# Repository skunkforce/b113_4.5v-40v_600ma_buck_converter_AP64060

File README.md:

# edgy_board number b113
This design is part of the [edgy board project](https://github.com/skunkforce/edgy_boards).  

# getting started
This repository uses submodules. After cloning use the command 

```$ git submodule update --init --recursive```

to pull the submodules before opening the project with kicad. 

# Tests
Tests can be found in [TESTS.md](TESTS.md)

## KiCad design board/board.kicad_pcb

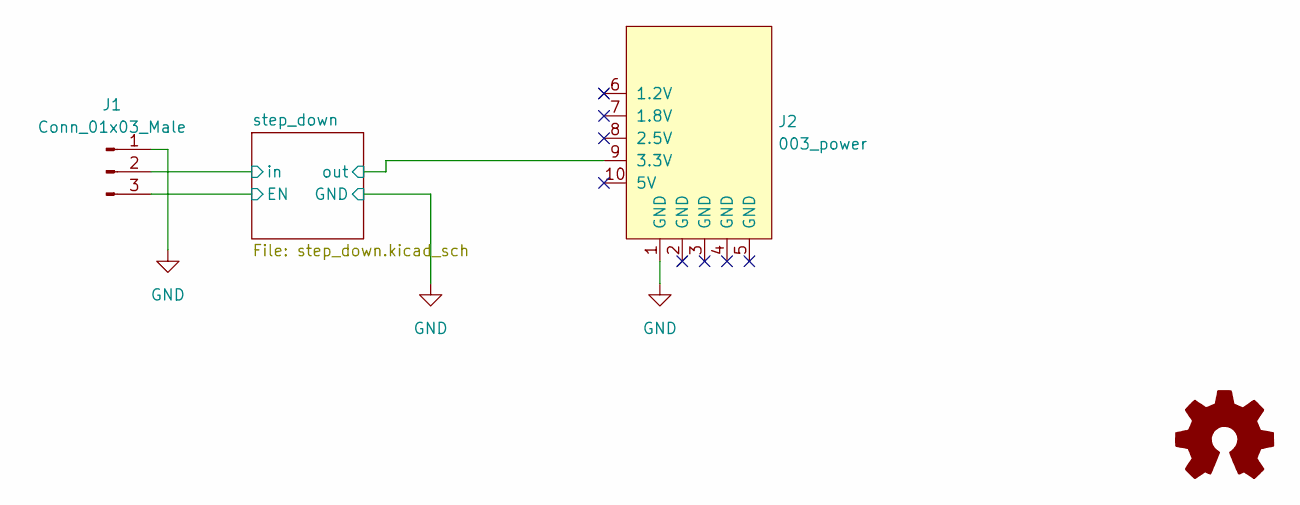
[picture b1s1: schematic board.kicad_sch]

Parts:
J1: Conn_01x03_Male; PinHeader_1x03_P2.54mm_Vertical
J2: 003_power; on_edge_2x05_host
LOGO1: Logo_Open_Hardware_Small; OSHW-Symbol_6.7x6mm_SilkScreen

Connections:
/step_down/EN: J1.3; also elsewhere on the board
/step_down/in: J1.2; also elsewhere on the board
/step_down/out: J2.9 (3.3V); also elsewhere on the board
GND: J1.1, J2.1 (GND); also elsewhere on the board

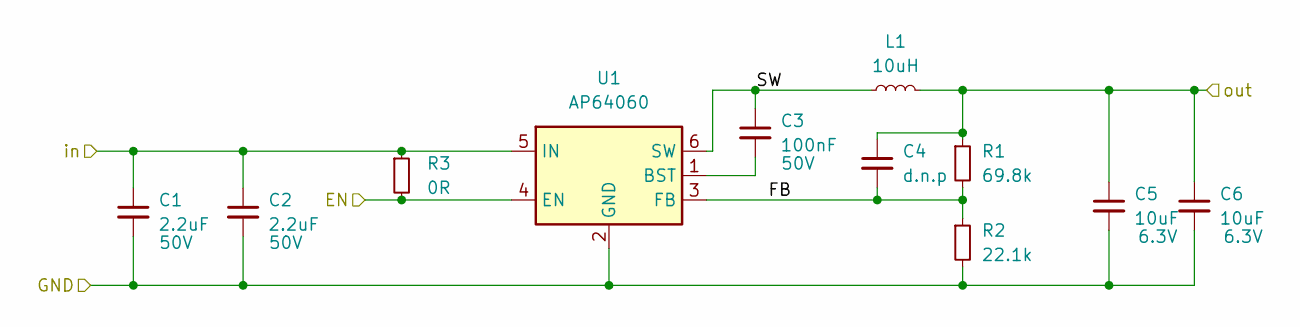
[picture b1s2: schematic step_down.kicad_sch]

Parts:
C1, C2: 2.2uF; C_1206_3216Metric; Voltage 50V
C3: 100nF; C_0603_1608Metric; Voltage 50V
C4: d.n.p; C_0603_1608Metric
C5, C6: 10uF; C_0603_1608Metric; Voltage 6.3V
L1: 10uH; L_1210_3225Metric; MPN CBC3225T100KR
R1: 69.8k; R_0603_1608Metric
R2: 22.1k; R_0603_1608Metric
R3: 0R; R_0402_1005Metric
U1: AP64060; TSOT-23-6

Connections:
/step_down/EN: R3.2, U1.4 (EN); also elsewhere on the board
/step_down/FB: C4.2, R1.2, R2.1, U1.3 (FB)
/step_down/SW: C3.1, L1.1, U1.6 (SW)
/step_down/in: C1.1, C2.1, R3.1, U1.5 (IN); also elsewhere on the board
/step_down/out: C4.1, C5.1, C6.1, L1.2, R1.1; also elsewhere on the board
GND: C1.2, C2.2, C5.2, C6.2, R2.2, U1.2 (GND); also elsewhere on the board
unnamed: C3.2, U1.1 (BST)

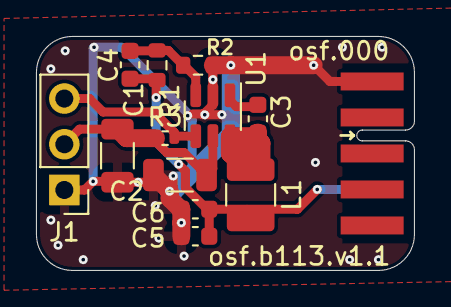
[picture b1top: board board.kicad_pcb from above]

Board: 2 copper layers, 21.0 x 13.0 mm, 14 parts (1 on the bottom side), 7 nets.

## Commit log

2023-03-17 initial
2023-05-04 fixed incorrect part number
2023-12-13 used lower dc resistance inductor
